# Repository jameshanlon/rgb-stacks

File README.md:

# RGB stacks

More details to come.

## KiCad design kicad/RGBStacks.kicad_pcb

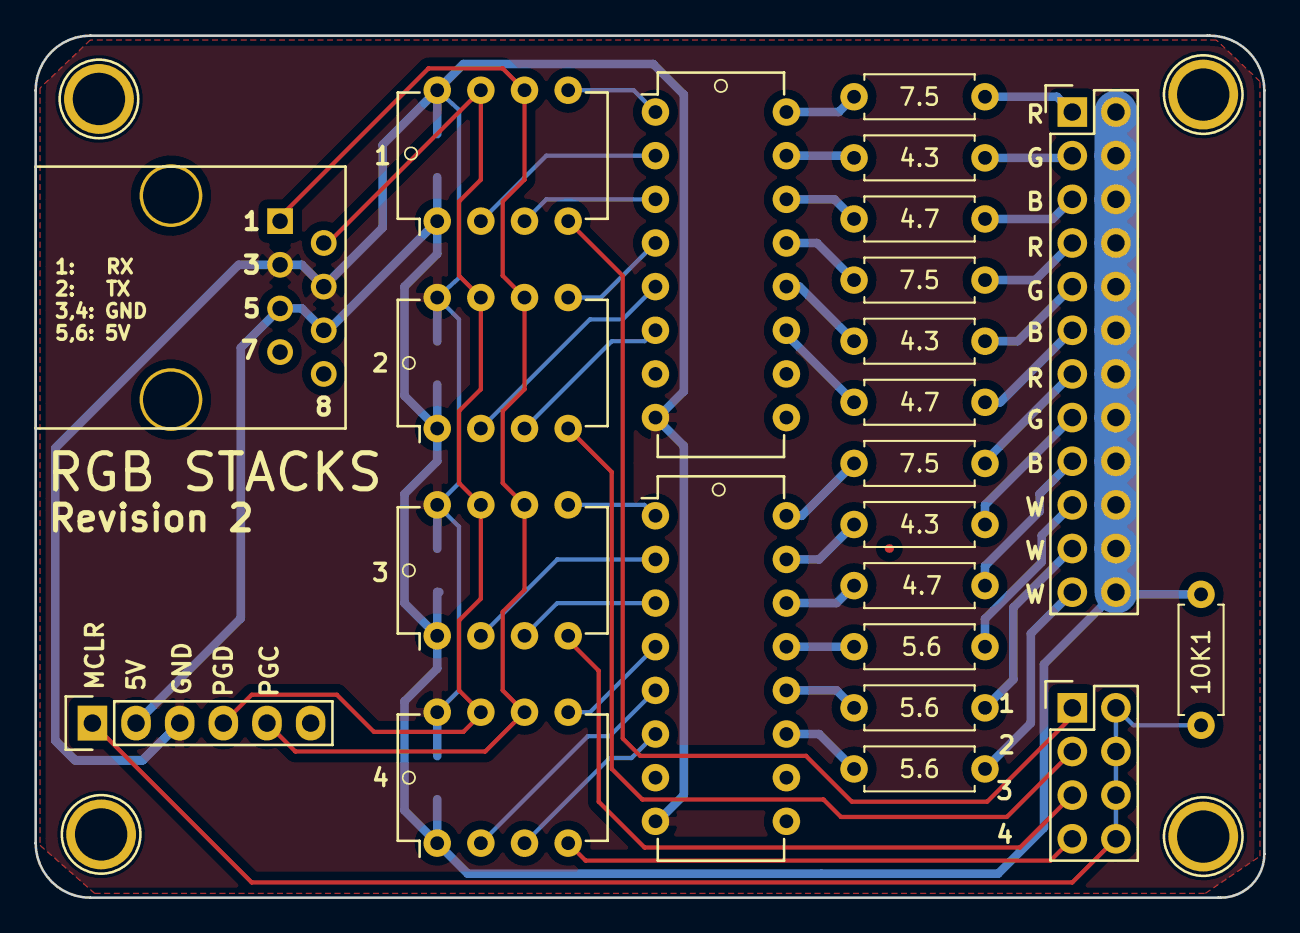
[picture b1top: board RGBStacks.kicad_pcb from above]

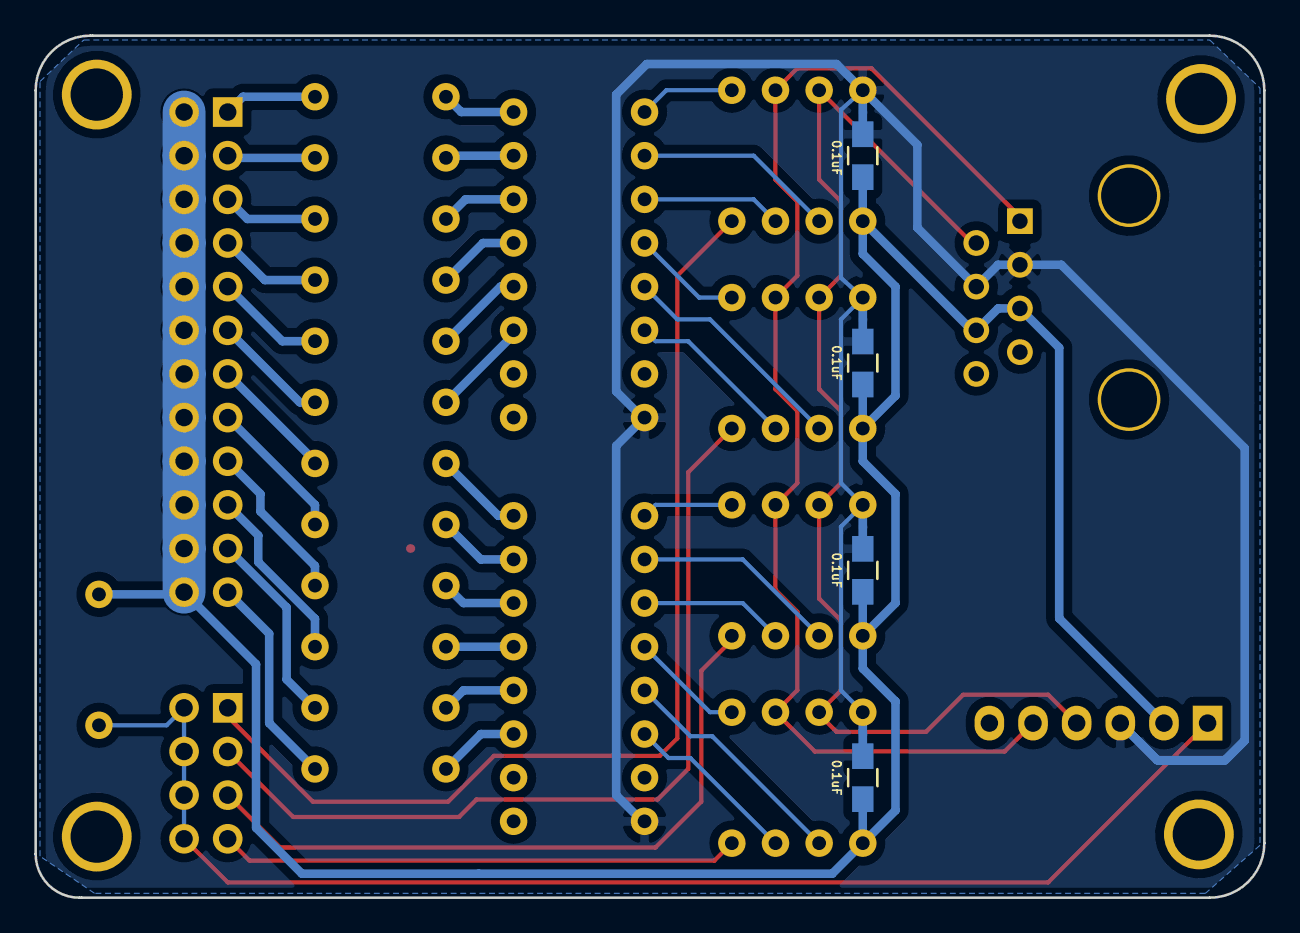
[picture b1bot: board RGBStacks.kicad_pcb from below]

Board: 2 copper layers, 71.5 x 50.2 mm, 27 parts (4 on the bottom side), 45 nets.

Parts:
4.3, 4.3#2, 4.3#3, 4.7, 4.7#2, 4.7#3, 5.6, 5.6#2, 5.6#3, 7.5, 7.5#2, 7.5#3, 10K1: R; R_Axial_DIN0207_L6.3mm_D2.5mm_P7.62mm_Horizontal
C1, C2, C3, C4: CP1; C_0805_HandSoldering
J1: RJ45_8
J2: CONN_01X06; Pin_Header_Straight_1x06
J3: CONN_02X12; Pin_Header_Straight_2x12
J4: CONN_02X04; Pin_Header_Straight_2x04
U1, U2, U3, U4: PIC12F1572; DIP-8_W7.62mm
U5, U6: ULN2003A; DIP-16_W7.62mm

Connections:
+5V: 10K1.1, C1.1, C2.1, C3.1, C4.1, J1.5, J1.6, J2.2, J3.2, J3.4, J3.6, J3.8, J3.10, J3.12, J3.14, J3.16, J3.18, J3.20, J3.22, J3.24, U1.1, U2.1, U3.1, U4.1
GND: C1.2, C2.2, C3.2, C4.2, J1.3, J1.4, J2.3, U1.8, U2.8, U3.8, U4.8, U5.8, U6.8
MCLR1: J4.1, U1.4
MCLR2: J4.3, U2.4
MCLR3: J4.5, U3.4
MCLR4: J4.7, U4.4
unnamed: 10K1.2, J2.1, J4.2, J4.4, J4.6, J4.8
unnamed: 7.5.1, J3.1
unnamed: 4.3.1, J3.3
unnamed: 4.7.1, J3.5
unnamed: 7.5#2.1, J3.7
unnamed: 4.3#2.1, J3.9
unnamed: 4.7#2.1, J3.11
unnamed: 7.5#3.1, J3.13
unnamed: 4.3#3.1, J3.15
unnamed: 4.7#3.1, J3.17
unnamed: 5.6.1, J3.19
unnamed: 5.6#2.1, J3.21
unnamed: 5.6#3.1, J3.23
unnamed: 7.5.2, U5.16
unnamed: 4.3.2, U5.15
unnamed: 4.7.2, U5.14
unnamed: 7.5#2.2, U5.13
unnamed: 4.3#2.2, U5.12
unnamed: 4.7#2.2, U5.11
unnamed: 7.5#3.2, U6.16
unnamed: 4.3#3.2, U6.15
unnamed: 4.7#3.2, U6.14
unnamed: 5.6.2, U6.13
unnamed: 5.6#2.2, U6.12
unnamed: 5.6#3.2, U6.11
unnamed: U1.2, U5.2
unnamed: U1.3, U5.3
unnamed: U1.5, U5.1
unnamed: U2.2, U5.5
unnamed: U2.3, U5.6
unnamed: U2.5, U5.4
unnamed: U3.2, U6.2
unnamed: U3.3, U6.3
unnamed: U3.5, U6.1
unnamed: U4.2, U6.5
unnamed: U4.3, U6.6
unnamed: U4.5, U6.4
RX/PGC: J1.1, J2.5, U1.6, U2.6, U3.6, U4.6
TX/PGD: J1.2, J2.4, U1.7, U2.7, U3.7, U4.7

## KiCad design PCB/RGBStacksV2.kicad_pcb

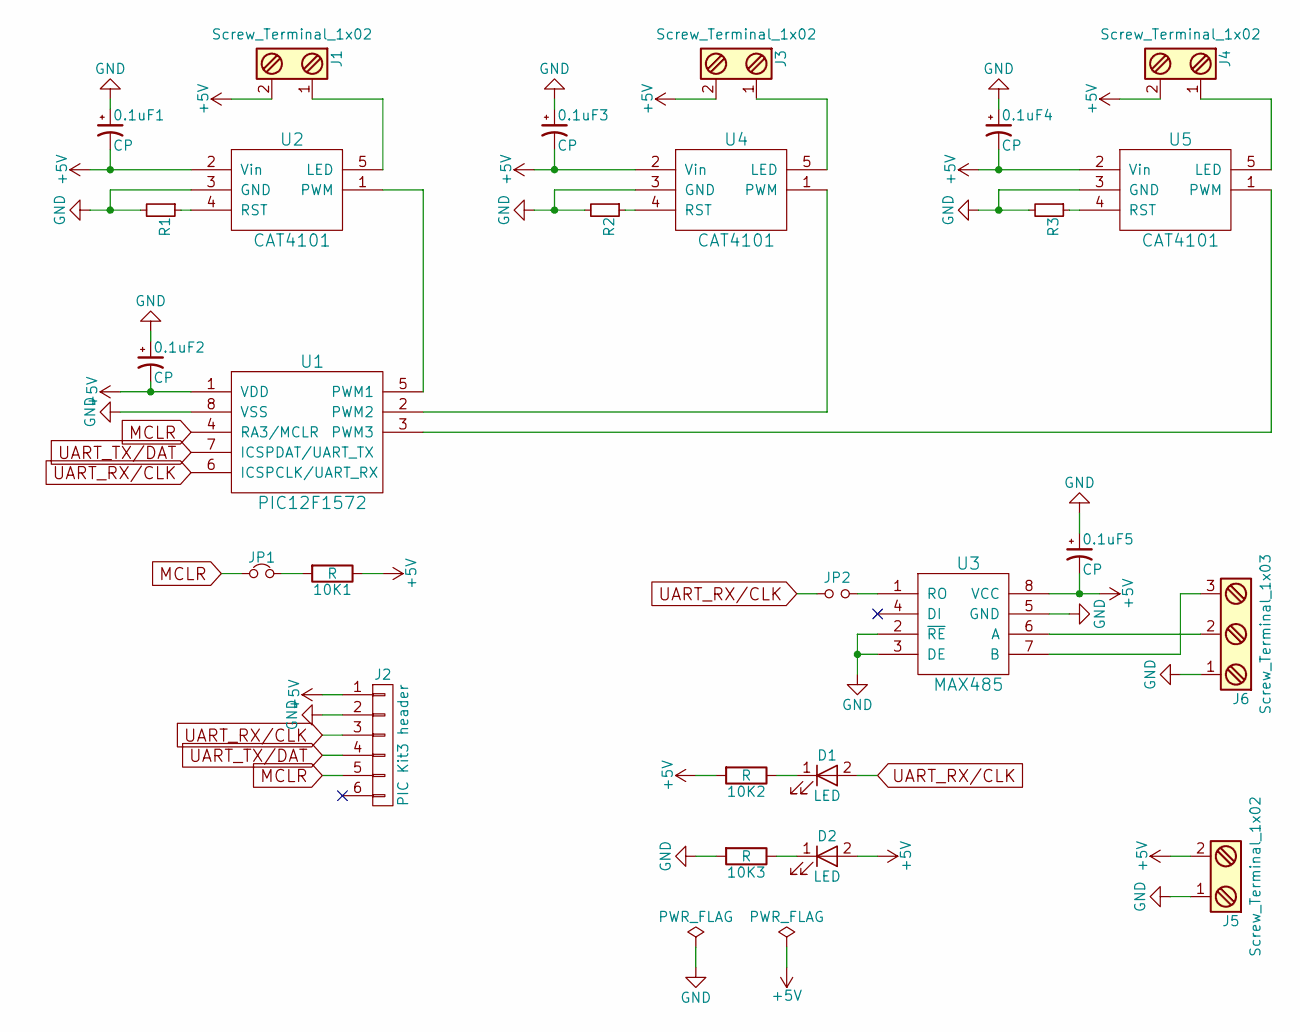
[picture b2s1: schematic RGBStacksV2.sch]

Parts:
0.1uF1, 0.1uF2, 0.1uF3, 0.1uF4, 0.1uF5: CP; C_0805_HandSoldering
10K1, 10K2, 10K3: R; R_0805_HandSoldering
D1, D2: LED; LED_0805
J1, J3, J4, J5: Screw_Terminal_1x02; TerminalBlock_Pheonix_MKDS1.5-2pol
J2: PIC Kit3 header; Pin_Header_Straight_1x06
J6: Screw_Terminal_1x03; TerminalBlock_Pheonix_MPT-2.54mm_3pol
JP1: Jumper_NC_Small; Pin_Header_Straight_1x02
JP2: Jumper_NO_Small; Pin_Header_Straight_1x02
R1, R2, R3: R_Small; R_0805_HandSoldering
U1: PIC12F1572; DIP-8_W7.62mm
U2, U4, U5: CAT4101; TO-263-5Lead
U3: MAX485; DIP-8_W7.62mm

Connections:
+5V: 0.1uF1.2, 0.1uF2.2, 0.1uF3.2, 0.1uF4.2, 0.1uF5.2, 10K1.1, 10K2.2, D2.2 (A), J1.2, J2.1, J3.2, J4.2, J5.2, U1.1 (VDD), U2.2 (Vin), U3.8 (VCC), U4.2 (Vin), U5.2 (Vin)
GND: 0.1uF1.1, 0.1uF2.1, 0.1uF3.1, 0.1uF4.1, 0.1uF5.1, 10K3.2, J2.2, J5.1, J6.1, R1.2, R2.2, R3.2, U1.8 (VSS), U2.3 (GND), U3.2 (~RE), U3.3 (DE), U3.5 (GND), U4.3 (GND), U5.3 (GND)
MCLR: J2.5, JP1.1, U1.4 (RA3/MCLR)
unnamed: 10K1.2, JP1.2
unnamed: 10K2.1, D1.1 (K)
unnamed: 10K3.1, D2.1 (K)
unnamed: J1.1, U2.5 (LED)
unnamed: J3.1, U4.5 (LED)
unnamed: J4.1, U5.5 (LED)
unnamed: J6.2, U3.6 (A)
unnamed: J6.3, U3.7 (B)
unnamed: JP2.2, U3.1 (RO)
unnamed: R1.1, U2.4 (RST)
unnamed: R2.1, U4.4 (RST)
unnamed: R3.1, U5.4 (RST)
unnamed: U1.2 (PWM2), U4.1 (PWM)
unnamed: U1.3 (PWM3), U5.1 (PWM)
unnamed: U1.5 (PWM1), U2.1 (PWM)
UART_RX/CLK: D1.2 (A), J2.3, JP2.1, U1.6 (ICSPCLK/UART_RX)
UART_TX/DAT: J2.4, U1.7 (ICSPDAT/UART_TX)

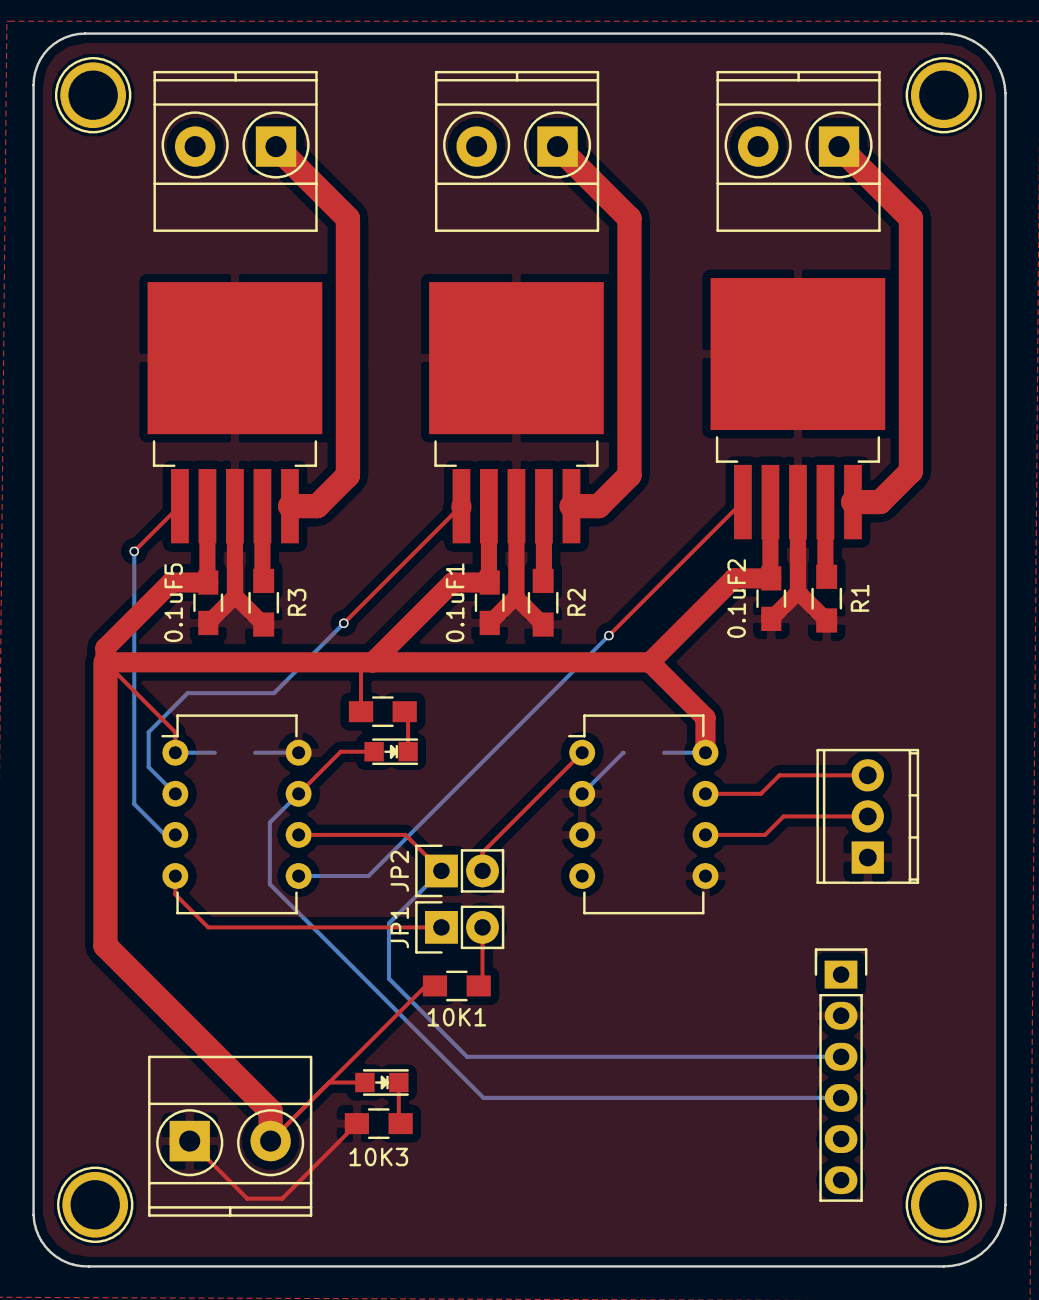
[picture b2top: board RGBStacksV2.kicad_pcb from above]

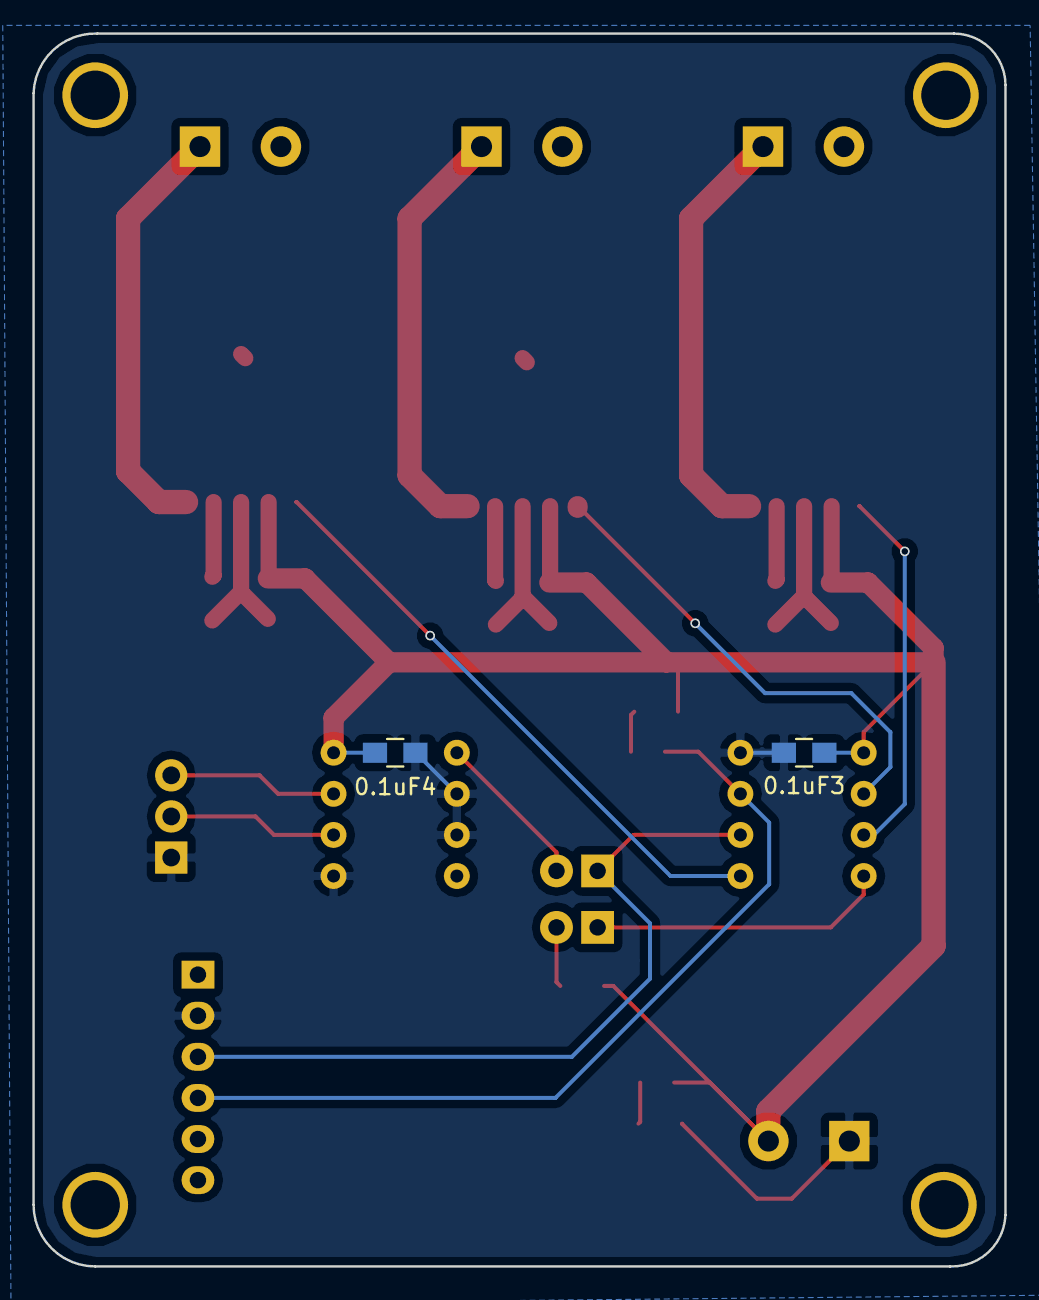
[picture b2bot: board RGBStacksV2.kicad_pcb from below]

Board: 2 copper layers, 60.1 x 76.2 mm, 26 parts (2 on the bottom side), 20 nets.

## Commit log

2016-06-19 Initial commit.
2017-06-04 Add KiCad PCB files.
2017-06-05 Update PCB designs.
2017-06-06 PCB tweaks.
2017-08-13 Beginnings of new PCB.
2018-01-24 Updated PCB.
2018-02-27 Remove old files
2018-02-27 Add initial controller script
2018-03-18 Update serial protocall to set all drivers at once
2018-03-18 MPLab project files update
2018-04-05 Tweaks for testing single packet frame
2018-04-05 Fixes to PIC driver program
2019-05-28 Fix PWMxPR indices
